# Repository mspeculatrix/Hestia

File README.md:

# HESTIA

A home robot project with the emphasis on sensors. The idea is that Hestia will autonomously patrol the home, keeping an eye on things. But it's really a way of playing with sensors.

This is a work in (slow) progress.

Hestia uses a distributed computing architecture. This consists of:

- **The Mainframe**: sounds impressive but it's probably going to be a Raspberry Pi or something similar. This does high-level stuff. It talks to...
- **Nodes**: These are microcontroller-based boards that perform specific functions, such as motor control, sensing etc. They talk to the Mainframe but also may also connect to several modules, most likely via SensorBus.
- **Modules**: These are semi-autonomous boards, each performing a single task, such as sensing, and communicating important information to (and receiving commands from) Nodes.

## CURRENT NODES

No specific Nodes have been designed so far. I've using an ATmega4809-based dev board for experimenting.

## CURRENT MODULES

- **sr04-1**: Ultrasonic rangefinder using the SensorBus HC-SR04 module board. Based on the ATtiny1604.
- **head_servo**: Uses the SensorBus servo module board to control two servos for pan & tilt operations on Hestia's sensor head. Based on the ATtiny1604.

## GIT BRANCHES

**Main**: Everything in this branch should be functional, but not necessarily complete. Basically, I use this branch as a 'safe' fallback if things go tits-up in the `dev` branch.

**dev**: This is where most of the work takes place. It always has the most up-to-date version of the project, but nothing is guaranteed to work. If you want to follow the project, this is where you should hang out.

**experimental**: For just trying stuff out, particularly stuff that I think is likely to fail. Anything in this branch should be considered temporary at best.

## OTHER REPOS FOR THIS PROJECT

- [Hestia Webserver](https://github.com/mspeculatrix/Hestia_Webserver) - a command and control server designed to be run off-robot.
- [Hestia Pico WS Server](https://github.com/mspeculatrix/Hestia_Pico_WS_Server) - a WebSocket server on the Raspberry Pi Pico 2W. Will provide an on-robot communications hub.

## SUPPORT THIS PROJECT

If you find this project in any way interesting or useful, you could consider [buying me a coffee](https://ko-fi.com/zolachrome).

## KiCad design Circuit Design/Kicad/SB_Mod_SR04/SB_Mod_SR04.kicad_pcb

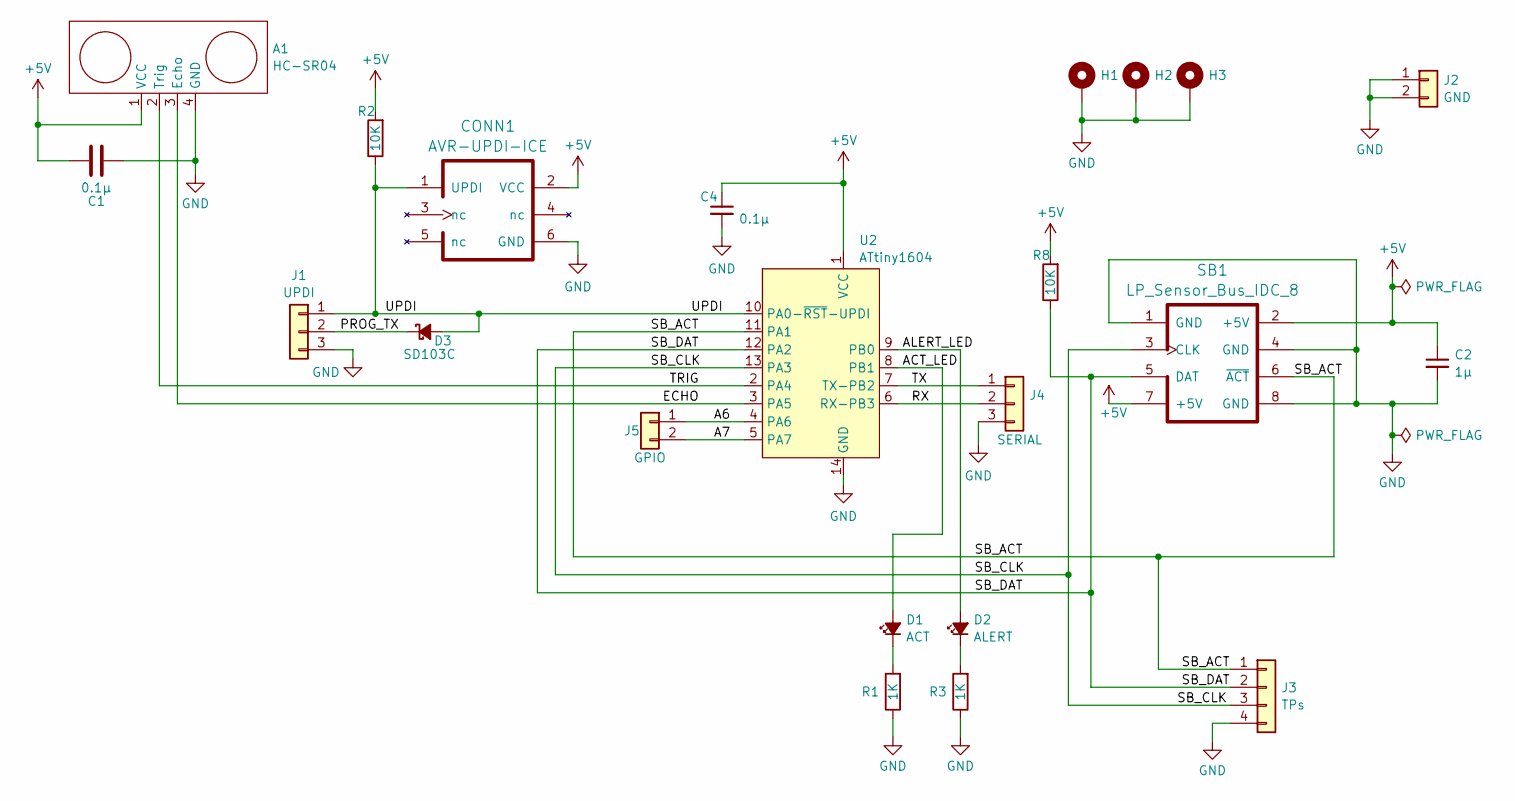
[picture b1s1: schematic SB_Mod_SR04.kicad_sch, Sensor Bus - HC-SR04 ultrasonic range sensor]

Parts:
A1: HC-SR04
C1, C4: 0.1µ; C_1206_3216Metric_Pad1.33x1.80mm_HandSolder
C2: 1µ; C_1206_3216Metric_Pad1.33x1.80mm_HandSolder
CONN1: AVR-UPDI-ICE; PinHeader_2x03_P2.54mm_Vertical
D1: ACT; LED_1206_SMD
D2: ALERT; LED_1206_SMD
D3: SD103C; D_SOD-123
H1, H2, H3: MountingHole_Pad; MountingHole_M3_Pad
J1: UPDI; PinHeader_1x03_P2.54mm_Vertical
J2: GND; PinHeader_1x02_P2.54mm_Vertical
J3: TPs; PinHeader_1x04_P2.54mm_Vertical
J4: SERIAL; PinHeader_1x03_P2.54mm_Vertical
J5: GPIO; PinHeader_1x02_P2.54mm_Vertical
R1, R3: 1K; Resistor_SMD_1206_HandSolder
R2, R8: 10K; Resistor_SMD_1206_HandSolder
SB1: LP_Sensor_Bus_IDC_8; SensorBus_2x04_P2.54mm_Vertical
U2: ATtiny1604; SOIC-14_3.9x8.7mm_P1.27mm

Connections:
+5V: A1.1 (VCC), C1.1, C2.1, C4.1, CONN1.2 (VCC), R2.2, R8.2, SB1.2 (+5V), SB1.7 (+5V), U2.1 (VCC)
/A6: J5.1, U2.4 (PA6)
/A7: J5.2, U2.5 (PA7)
/ACT_LED: D1.2 (A), U2.8 (PB1)
/ALERT_LED: D2.2 (A), U2.9 (PB0)
/ECHO: A1.3 (Echo), U2.3 (PA5)
/PROG_TX: D3.1 (K), J1.2
/RX: J4.2, U2.6 (RX-PB3)
/SB_ACT: J3.1, SB1.6 (~ACT), U2.11 (PA1)
/SB_CLK: J3.3, SB1.3 (CLK), U2.13 (PA3)
/SB_DAT: J3.2, R8.1, SB1.5 (DAT), U2.12 (PA2)
/TRIG: A1.2 (Trig), U2.2 (PA4)
/TX: J4.1, U2.7 (TX-PB2)
/UPDI: CONN1.1 (UPDI), D3.2 (A), J1.1, R2.1, U2.10 (PA0-~RST-UPDI)
GND: A1.4 (GND), C1.2, C2.2, C4.2, CONN1.6 (GND), H1.1, H2.1, H3.1, J1.3, J2.1, J2.2, J3.4, J4.3, R1.1, R3.1, SB1.1 (GND), SB1.4 (GND), SB1.8 (GND), U2.14 (GND)
unnamed: D1.1 (K), R1.2
unnamed: D2.1 (K), R3.2

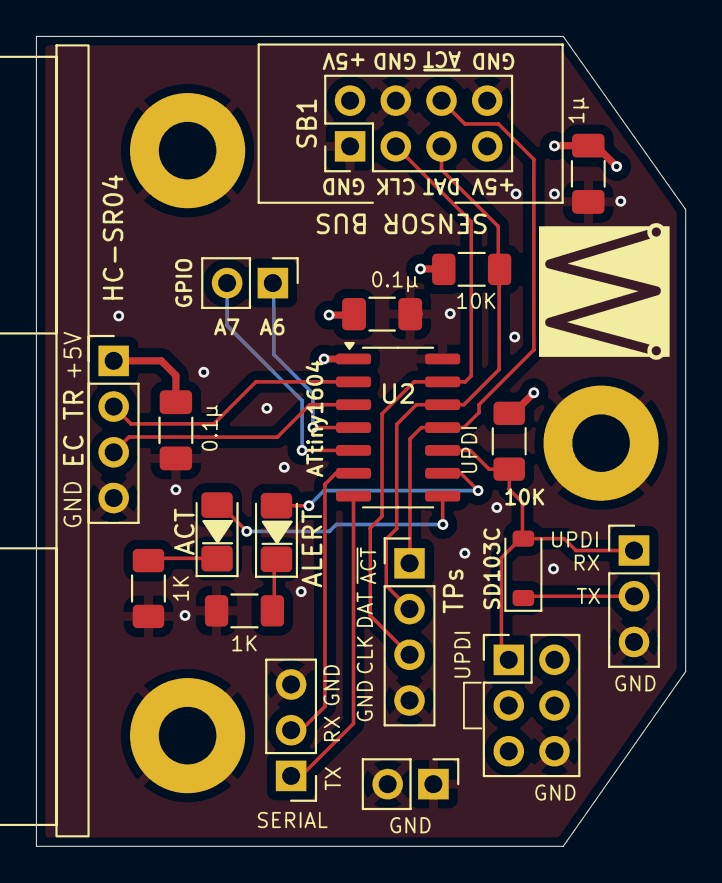
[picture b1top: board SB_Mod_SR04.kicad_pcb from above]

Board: 4 copper layers, 36.1 x 45.0 mm, 22 parts (0 on the bottom side), 17 nets.

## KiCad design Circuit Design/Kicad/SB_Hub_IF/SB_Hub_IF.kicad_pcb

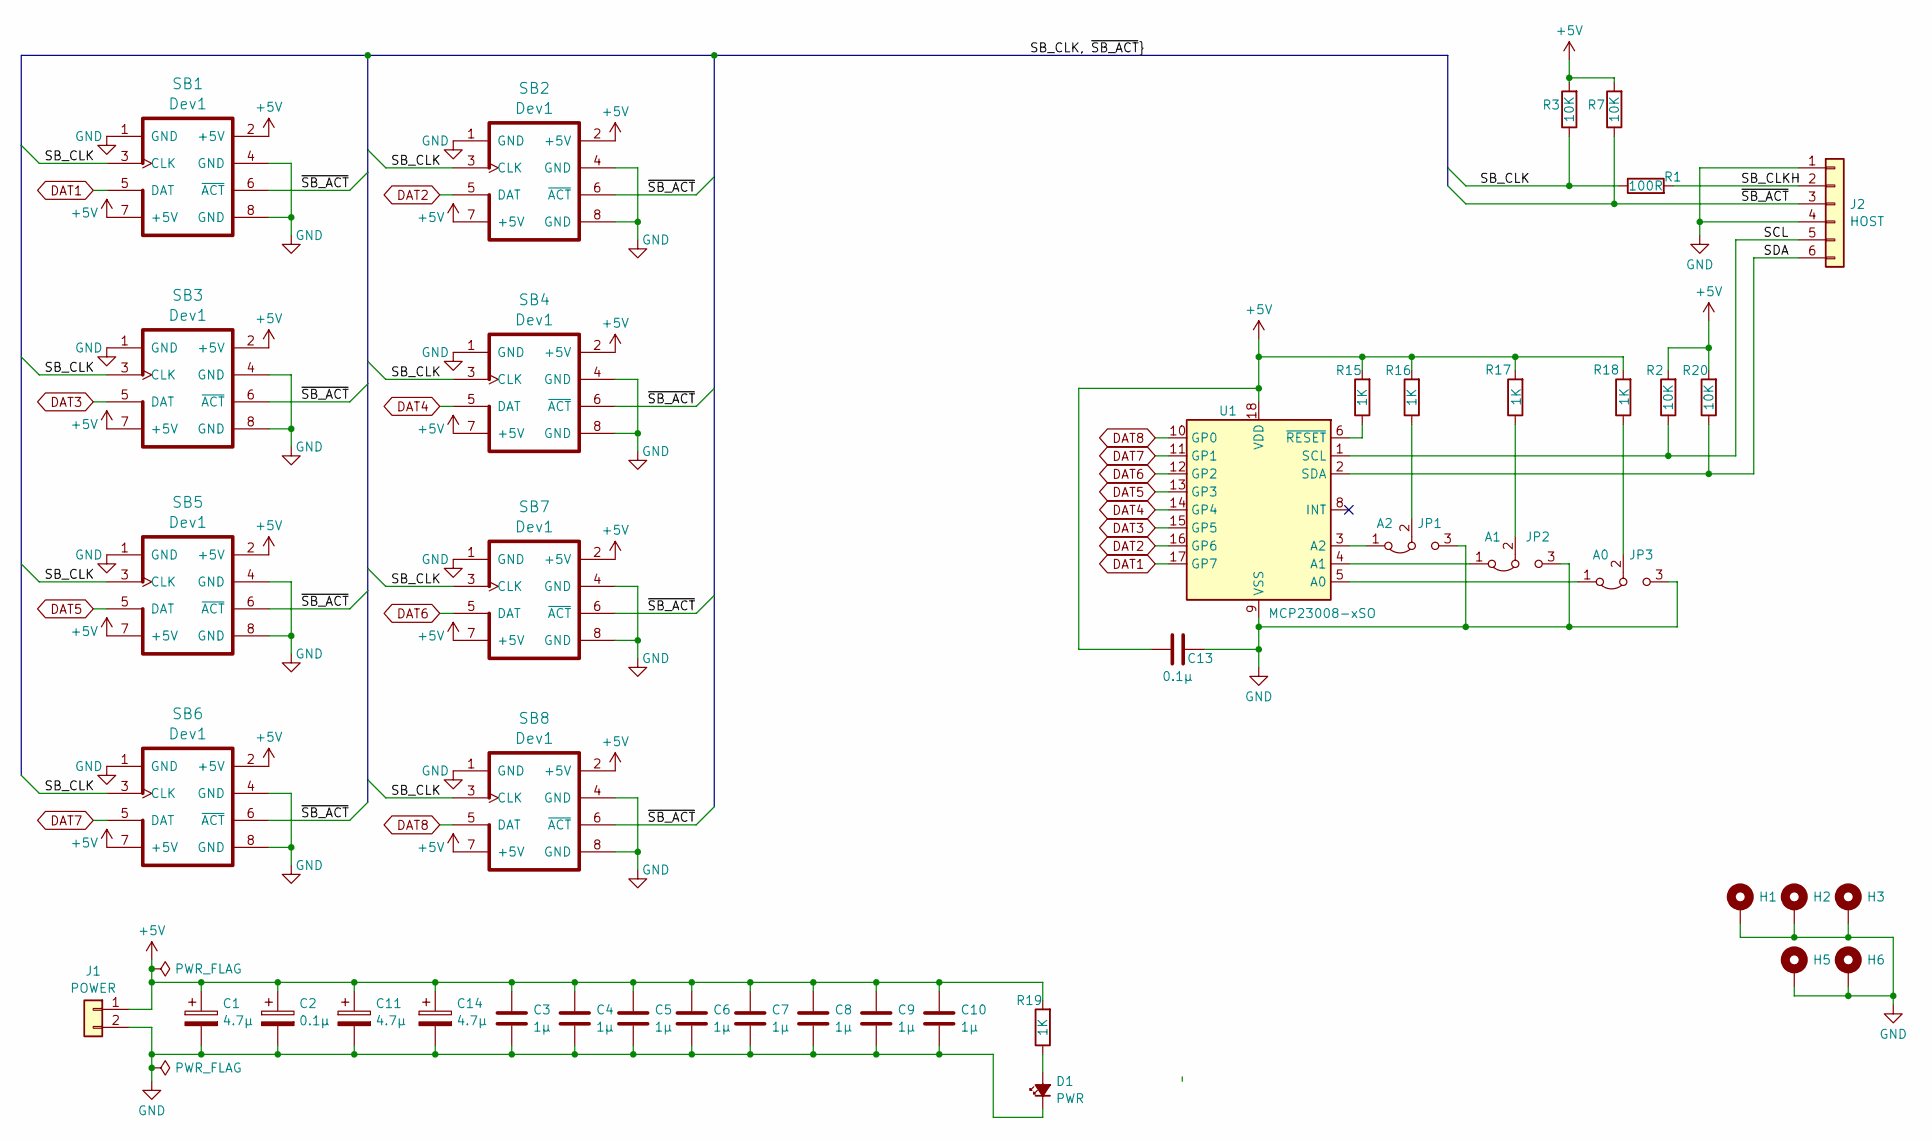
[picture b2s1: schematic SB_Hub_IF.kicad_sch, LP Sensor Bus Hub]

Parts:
C1, C11, C14: 4.7µ; Cap_THT_1µF_polarised
C2: 0.1µ; Cap_THT_0.1µF_polarised
C3, C4, C5, C6, C7, C8, C9, C10: 1µ; C_1206_3216Metric_Pad1.33x1.80mm_HandSolder
C13: 0.1µ; C_1206_3216Metric_Pad1.33x1.80mm_HandSolder
D1: PWR; LED_1206_SMD
H1, H2, H3, H5, H6: MountingHole_Pad; MountingHole_M3_Pad
J1: POWER; PinHeader_1x02_P2.54mm_Vertical
J2: HOST; PinHeader_1x06_P2.54mm_Horizontal
JP1: A2; PinHeader_1x03_P2.54mm_Vertical
JP2: A1; PinHeader_1x03_P2.54mm_Vertical
JP3: A0; PinHeader_1x03_P2.54mm_Vertical
R1: 100R; Resistor_SMD_1206_HandSolder
R2, R3, R7, R20: 10K; Resistor_SMD_1206_HandSolder
R15, R16, R17, R18, R19: 1K; Resistor_SMD_1206_HandSolder
SB1, SB2, SB3, SB4, SB5, SB6, SB7, SB8: Dev1; SensorBus_2x04_P2.54mm_Vertical
U1: MCP23008-xSO; SOIC-18W_7.5x11.6mm_P1.27mm

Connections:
+5V: C1.1, C2.1, C3.1, C4.1, C5.1, C6.1, C7.1, C8.1, C9.1, C10.1, C11.1, C13.1, C14.1, J1.1, R2.2, R3.2, R7.2, R15.2, R16.2, R17.2, R18.2, R19.2, R20.2, SB1.2 (+5V), SB1.7 (+5V), SB2.2 (+5V), SB2.7 (+5V), SB3.2 (+5V), SB3.7 (+5V), SB4.2 (+5V), SB4.7 (+5V), SB5.2 (+5V), SB5.7 (+5V), SB6.2 (+5V), SB6.7 (+5V), SB7.2 (+5V), SB7.7 (+5V), SB8.2 (+5V), SB8.7 (+5V), U1.18 (VDD)
/SB_CLK: R1.1, R3.1, SB1.3 (CLK), SB2.3 (CLK), SB3.3 (CLK), SB4.3 (CLK), SB5.3 (CLK), SB6.3 (CLK), SB7.3 (CLK), SB8.3 (CLK)
/SB_CLKH: J2.2, R1.2
/SCL: J2.5, R2.1, U1.1 (SCL)
/SDA: J2.6, R20.1, U1.2 (SDA)
/~SB_ACT: J2.3, R7.1, SB1.6 (~ACT), SB2.6 (~ACT), SB3.6 (~ACT), SB4.6 (~ACT), SB5.6 (~ACT), SB6.6 (~ACT), SB7.6 (~ACT), SB8.6 (~ACT)
DAT1: SB1.5 (DAT), U1.17 (GP7)
DAT2: SB2.5 (DAT), U1.16 (GP6)
DAT3: SB3.5 (DAT), U1.15 (GP5)
DAT4: SB4.5 (DAT), U1.14 (GP4)
DAT5: SB5.5 (DAT), U1.13 (GP3)
DAT6: SB7.5 (DAT), U1.12 (GP2)
DAT7: SB6.5 (DAT), U1.11 (GP1)
DAT8: SB8.5 (DAT), U1.10 (GP0)
GND: C1.2, C2.2, C3.2, C4.2, C5.2, C6.2, C7.2, C8.2, C9.2, C10.2, C11.2, C13.2, C14.2, D1.1 (K), H1.1, H2.1, H3.1, H5.1, H6.1, J1.2, J2.1, J2.4, JP1.3 (B), JP2.3 (B), JP3.3 (B), SB1.1 (GND), SB1.4 (GND), SB1.8 (GND), SB2.1 (GND), SB2.4 (GND), SB2.8 (GND), SB3.1 (GND), SB3.4 (GND), SB3.8 (GND), SB4.1 (GND), SB4.4 (GND), SB4.8 (GND), SB5.1 (GND), SB5.4 (GND), SB5.8 (GND), SB6.1 (GND), SB6.4 (GND), SB6.8 (GND), SB7.1 (GND), SB7.4 (GND), SB7.8 (GND), SB8.1 (GND), SB8.4 (GND), SB8.8 (GND), U1.9 (VSS)
unnamed: D1.2 (A), R19.1
unnamed: JP1.1 (A), U1.3 (A2)
unnamed: JP1.2 (C), R16.1
unnamed: JP2.1 (A), U1.4 (A1)
unnamed: JP2.2 (C), R17.1
unnamed: JP3.1 (A), U1.5 (A0)
unnamed: JP3.2 (C), R18.1
unnamed: R15.1, U1.6 (~RESET)

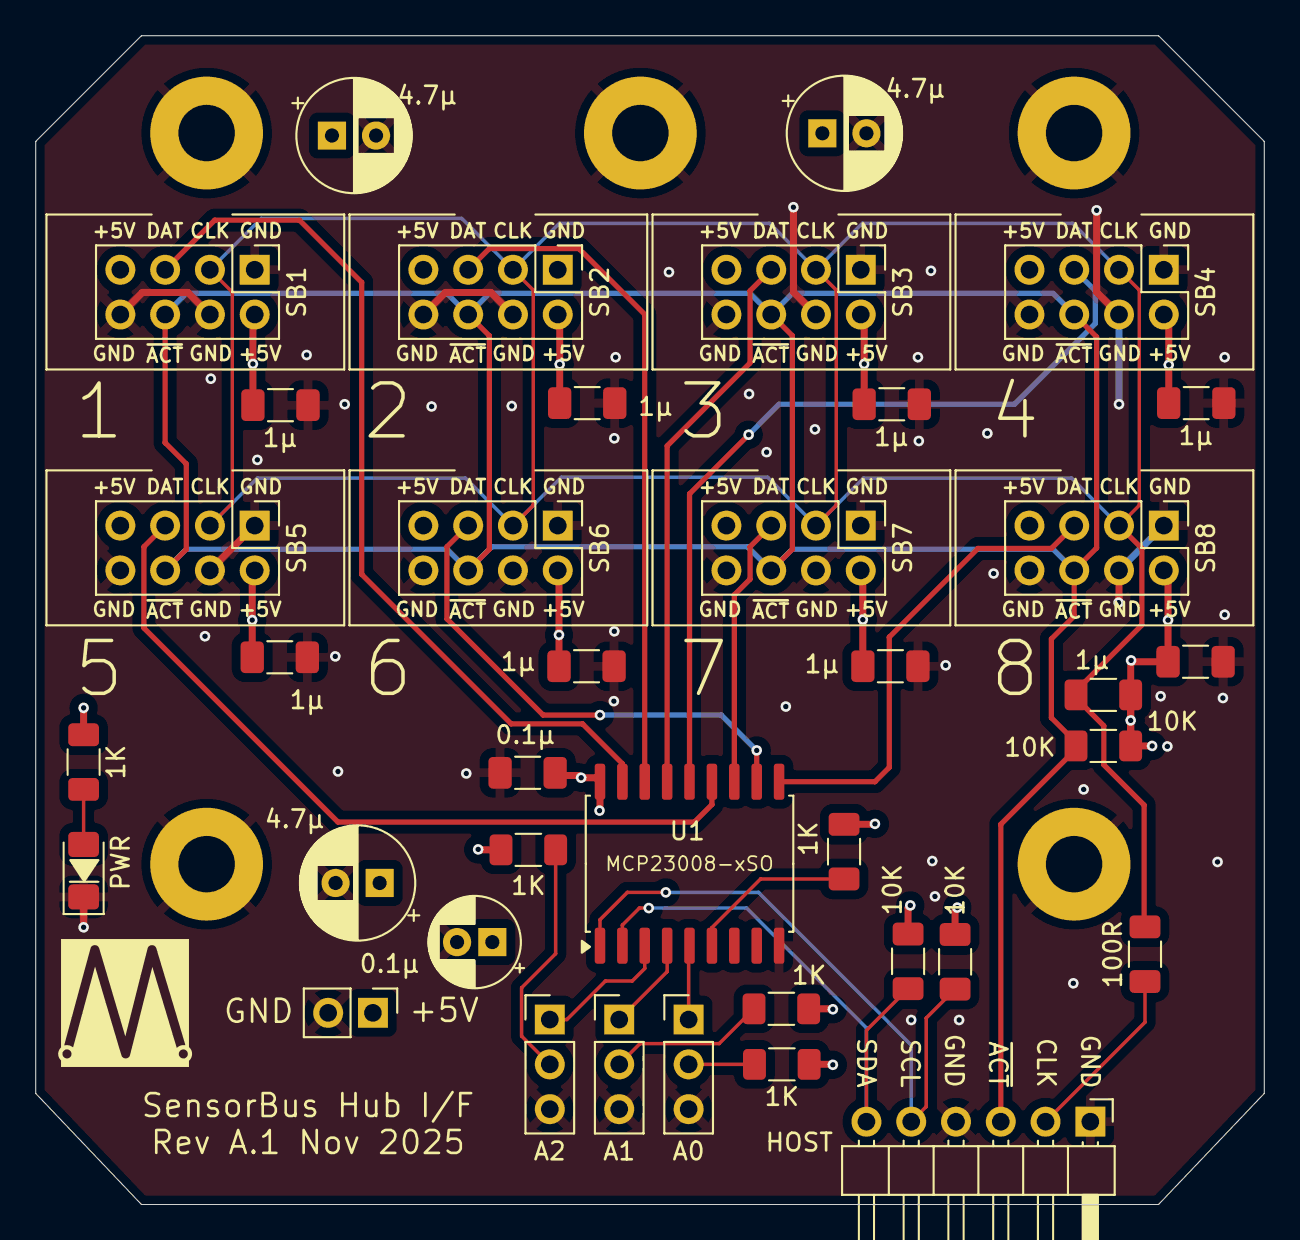
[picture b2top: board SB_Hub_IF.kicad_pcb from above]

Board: 4 copper layers, 69.7 x 66.3 mm, 43 parts (0 on the bottom side), 23 nets.

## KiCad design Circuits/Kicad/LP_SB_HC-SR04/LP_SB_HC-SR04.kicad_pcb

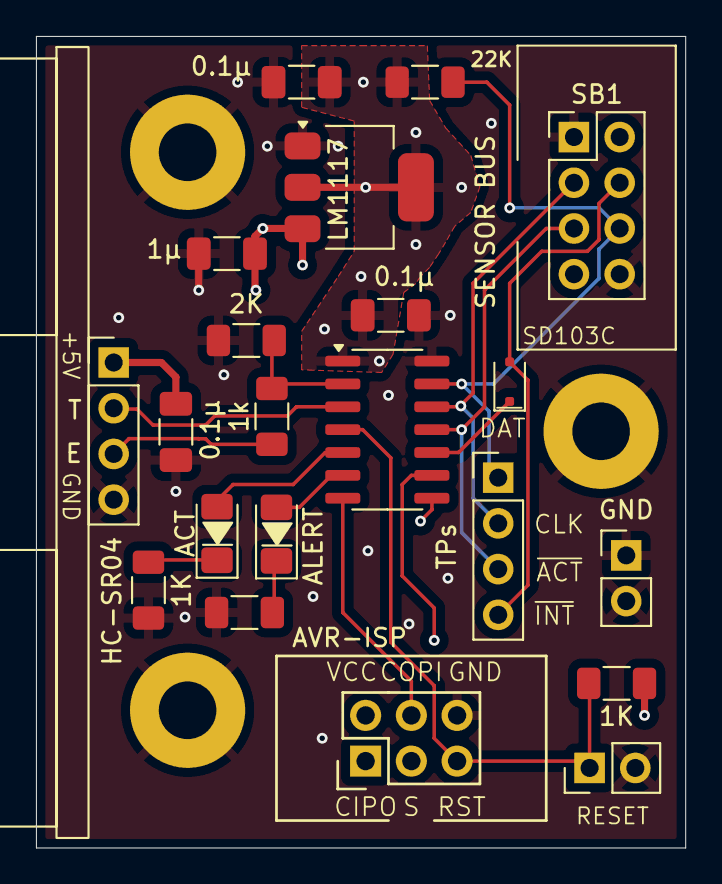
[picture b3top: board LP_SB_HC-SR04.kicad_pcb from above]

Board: 4 copper layers, 36.1 x 45.1 mm, 24 parts (0 on the bottom side), 19 nets.

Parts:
A1: HC-SR04
C1, C4, C5: 0.1µ; C_1206_3216Metric_Pad1.33x1.80mm_HandSolder
C2: 1µ; C_1206_3216Metric_Pad1.33x1.80mm_HandSolder
CONN1: AVR-ISP; AVR_ISP_HE10_2x3
D1: ACT; LED_1206_SMD
D2: ALERT; LED_1206_SMD
D3: SD103C; D_SOD-323F
H1, H2, H3: MountingHole_Pad; MountingHole_M3_Pad
J1: TPs; PinHeader_1x04_P2.54mm_Vertical
J2: GND; PinHeader_1x02_P2.54mm_Vertical
J3: RESET; PinHeader_1x02_P2.54mm_Vertical
LM1: LM1117; SOT-223-3_TabPin2
R1, R2, R3: 1K; Resistor_SMD_1206_HandSolder
R8: 22K; Resistor_SMD_1206_HandSolder
R9: 1k; Resistor_SMD_1206_HandSolder
R10: 2K; Resistor_SMD_1206_HandSolder
SB1: LP_Sensor_Bus_IDC_8; SensorBus_2x04_P2.54mm_Vertical
U1: ATTINY84A; SOIC-14_3.9x8.7mm_P1.27mm

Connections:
+3V3: C4.1, C5.2, LM1.2 (Vout), R2.2, R8.2, U1.1 (VCC)
+5V: A1.1 (VCC), C1.1, C2.1, CONN1.2 (VCC), LM1.3 (Vin), SB1.2 (+5V), SB1.7 (+5V)
/ACT_LED: D1.2 (A), U1.5 (PB2)
/ALERT_LED: D2.2 (A), U1.6 (PA7)
/CIPO: CONN1.1 (CIPO), U1.8 (PA5)
/COPI: CONN1.4 (COPI), U1.7 (PA6)
/ECHO_H: A1.3 (Echo), R9.2
/ECHO_L: R9.1, R10.2, U1.2 (PB0)
/SB_CLK: J1.2, SB1.3 (CLK), U1.12 (PA1)
/SB_DAT: J1.1, R8.1, SB1.6 (DAT), U1.13 (PA0)
/SCK: CONN1.3 (SCK), U1.9 (PA4)
/TRIG: A1.2 (Trig), U1.3 (PB1)
/~RESET: CONN1.5 (RESET), J3.1, R2.1, U1.4 (PB3)
/~SB_ACT: J1.3, SB1.5 (~ACT), U1.11 (PA2)
/~SB_INT: D3.2 (A), J1.4, SB1.4 (~INT)
/~SB_INTP: D3.1 (K), U1.10 (PA3)
GND: A1.4 (GND), C1.2, C2.2, C4.2, C5.1, CONN1.6 (GND), H1.1, H2.1, H3.1, J2.1, J2.2, J3.2, LM1.1 (GND), R1.1, R3.1, R10.1, SB1.1 (GND), SB1.8 (GND), U1.14 (GND)
unnamed: D1.1 (K), R1.2
unnamed: D2.1 (K), R3.2

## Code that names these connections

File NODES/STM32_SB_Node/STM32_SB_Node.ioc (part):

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Mcu.Name=STM32H503RBTx
Mcu.Package=LQFP64
Mcu.UserName=STM32H503RBTx
PA13(JTMS/SWDIO).GPIOParameters=GPIO_Label
PA13(JTMS/SWDIO).GPIO_Label=T_SWDIO
PA13(JTMS/SWDIO).Signal=DEBUG_JTMS-SWDIO
PA14(JTCK/SWCLK).GPIOParameters=GPIO_Label
PA14(JTCK/SWCLK).GPIO_Label=T_SWCLK
PA14(JTCK/SWCLK).Signal=DEBUG_JTCK-SWCLK
PA15(JTDI).GPIOParameters=GPIO_Label
PA15(JTDI).GPIO_Label=T_JTDI
PA15(JTDI).Signal=DEBUG_JTDI
PA3.Signal=USART3_RX
PA4.Signal=USART3_TX
PB14.GPIOParameters=GPIO_Label
PB14.GPIO_Label=ARD_D1_TX
PB14.Signal=USART1_TX
PB15.GPIOParameters=GPIO_Label
PB15.GPIO_Label=ARD_D0_RX
PB15.Signal=USART1_RX
PB3(JTDO/TRACESWO).GPIOParameters=GPIO_Label
PB3(JTDO/TRACESWO).GPIO_Label=T_SWO
PB3(JTDO/TRACESWO).Signal=DEBUG_JTDO-SWO
PC0.GPIOParameters=GPIO_Label
PC0.GPIO_Label=SB_CLK
PC0.Signal=GPIO_Input
PC1.GPIOParameters=GPIO_Label
PC1.GPIO_Label=SB_ACT
PC1.Signal=GPIO_Input
PC10.GPIOParameters=GPIO_PuPd,GPIO_Label,GPIO_ModeDefaultEXTI
PC10.GPIO_Label=DAT2
PC10.GPIO_ModeDefaultEXTI=GPIO_MODE_IT_FALLING
PC10.GPIO_PuPd=GPIO_PULLUP
PC10.Signal=GPXTI10
PC11.GPIOParameters=GPIO_PuPd,GPIO_Label,GPIO_ModeDefaultEXTI
PC11.GPIO_Label=DAT3
PC11.GPIO_ModeDefaultEXTI=GPIO_MODE_IT_FALLING
PC11.GPIO_PuPd=GPIO_PULLUP
PC11.Signal=GPXTI11
PC12.GPIOParameters=GPIO_PuPd,GPIO_Label,GPIO_ModeDefaultEXTI
PC12.GPIO_Label=DAT4
PC12.GPIO_ModeDefaultEXTI=GPIO_MODE_IT_FALLING
PC12.GPIO_PuPd=GPIO_PULLUP
PC12.Signal=GPXTI12
PC13.GPIOParameters=GPIO_PuPd,GPIO_Label,GPIO_ModeDefaultEXTI
PC13.GPIO_Label=DAT5
PC13.GPIO_ModeDefaultEXTI=GPIO_MODE_IT_FALLING
PC13.GPIO_PuPd=GPIO_PULLUP
PC13.Signal=GPXTI13
PC14-OSC32_IN(OSC32_IN).GPIOParameters=GPIO_PuPd,GPIO_Label,GPIO_ModeDefaultEXTI
PC14-OSC32_IN(OSC32_IN).GPIO_Label=DAT6
PC14-OSC32_IN(OSC32_IN).GPIO_ModeDefaultEXTI=GPIO_MODE_IT_FALLING
PC14-OSC32_IN(OSC32_IN).GPIO_PuPd=GPIO_PULLUP
PC14-OSC32_IN(OSC32_IN).Signal=GPXTI14
PC15-OSC32_OUT(OSC32_OUT).GPIOParameters=GPIO_PuPd,GPIO_Label,GPIO_ModeDefaultEXTI
PC15-OSC32_OUT(OSC32_OUT).GPIO_Label=DAT7
PC15-OSC32_OUT(OSC32_OUT).GPIO_ModeDefaultEXTI=GPIO_MODE_IT_FALLING
PC15-OSC32_OUT(OSC32_OUT).GPIO_PuPd=GPIO_PULLUP
PC15-OSC32_OUT(OSC32_OUT).Signal=GPXTI15
PC8.GPIOParameters=GPIO_PuPd,GPIO_Label,GPIO_ModeDefaultEXTI
PC8.GPIO_Label=DAT0
PC8.GPIO_ModeDefaultEXTI=GPIO_MODE_IT_FALLING
PC8.GPIO_PuPd=GPIO_PULLUP
PC8.Signal=GPXTI8
PC9.GPIOParameters=GPIO_PuPd,GPIO_Label,GPIO_ModeDefaultEXTI
PC9.GPIO_Label=DAT1
PC9.GPIO_ModeDefaultEXTI=GPIO_MODE_IT_FALLING
PC9.GPIO_PuPd=GPIO_PULLUP
PC9.Signal=GPXTI9
PH0-OSC_IN(PH0).Mode=HSE-External-Oscillator
PH0-OSC_IN(PH0).Signal=RCC_OSC_IN
PH1-OSC_OUT(PH1).Mode=HSE-External-Oscillator
PH1-OSC_OUT(PH1).Signal=RCC_OSC_OUT
RCC.HSE_VALUE=24000000
RCC.SYSCLKFreq_VALUE=250000000
RCC.SYSCLKSource=RCC_SYSCLKSOURCE_PLLCLK
board=NUCLEO-H503RB
boardIOC=true

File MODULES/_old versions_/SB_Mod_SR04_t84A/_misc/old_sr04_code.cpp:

/*
 * SmartHCSR04.cpp
 *
 * Created: 11/27/2018 12:32:39 PM
 * Author : Steve
 */
#ifndef F_CPU
#define F_CPU 1000000UL
#endif

#include <avr/io.h>
#include <util/delay.h>
#include <string.h>
#include <stdio.h>
#include <smd_avr_usi_i2clib.h>
#include <uproc/smd_attiny_24_44_84A.h>
 //#include <smd_avr_sensorbuslib.h>

#define TRIG_PIN PA1			// orange
#define ECHO_PIN PA2			// yellow
#define ALERT_PIN PA3			// goes low to alert hub
#define LCD_I2C_ADDR 0xC6
#define MAX_ECHO_TIME 23200		// 23200us is 400cm max range.
#define DIST_FACTOR 58

#define ALERT_PULSE_TIME 50		// us
#define ALERT_INTERVAL 500		// ms - minimum time between alert signals - blocking

#define DEFAULT_ALERT_DIST 15	// cm

void displayMsg(const char msg[], uint8_t x, uint8_t y) {
	USI_I2C_start(LCD_I2C_ADDR, I2C_WRITE_MODE);
	USI_I2C_sendByte(0);	// command register
	USI_I2C_sendByte(3);	// position cursor command
	USI_I2C_sendByte(y);	// x pos : first col
	USI_I2C_sendByte(x);	// y pos
	for (uint8_t i = 0; i < strlen(msg); i++) {
		USI_I2C_sendByte(char(msg[i]));
	}
	// clear rest of line with spaces
	//for(uint8_t i = strlen(msg); i < 12; i++) {
	//USI_I2C_sendByte(0x20);	// space
	//}
	USI_I2C_stop();
}

void displayClear() {
	USI_I2C_start(LCD_I2C_ADDR, I2C_WRITE_MODE);
	USI_I2C_sendByte(0);	// command register
	USI_I2C_sendByte(12);
	USI_I2C_stop();
}

void displayInit() {
	USI_I2C_start(LCD_I2C_ADDR, I2C_WRITE_MODE);
	USI_I2C_sendByte(0);	// command register
	USI_I2C_sendByte(4);	// cursor off
	USI_I2C_sendByte(12);	// clear screen, home cursor
	USI_I2C_sendByte(19);	// backlight on
	USI_I2C_stop();
}

uint16_t ping(void) {
	unsigned long elapsed = 0;
	uint16_t distance = 0;
	PORTA |= (1 << TRIG_PIN);				// set trigger pin high
	_delay_us(10);							// wait for min. 10us
	PORTA &= ~(1 << TRIG_PIN);				// take trigger pin low again
	while ((PINA & (1 << ECHO_PIN)) == 0);	// loop until echo pin goes high
	TCNT1 = 0;								// reset timer
	while (PINA & (1 << ECHO_PIN));			// loop until echo pin goes low again
	elapsed = TCNT1;						// read timer
	// at clock speed of 1MHz, elapsed will be number of us for echo time.
	// This should be well within range of 16-bit int (TCNT1 is 16-bit).
	// With higher clock speeds, elapsed is going to be much higher and
	// may need scaling
	elapsed = elapsed / (F_CPU / 1000000.0);	// to scale for clock speed, but here we're diving by 1 !
	if (elapsed <= MAX_ECHO_TIME) {
		distance = (uint16_t)(elapsed / DIST_FACTOR);
	}
	return distance;
}

// MAIN OBJECTS
//SensorBus ssb = SensorBus();

int main(void) {
	// ----------------------------------------------------------------------------------------------------
	// -----  SETUP                                                                                   -----
	// ----------------------------------------------------------------------------------------------------
	DDRA = 0;	// actually defaults to this, but let's be specific
	DDRA |= (1 << TRIG_PIN);		// Trigger pin as output
	DDRA |= (1 << ALERT_PIN);		// Alert pin as output
	PORTA &= ~(1 << TRIG_PIN);		// set trigger pin low
	PORTA |= (1 << ALERT_PIN);		// set alert pin high (it's active low)
	TCCR1B |= (1 << CS10);			// set prescaler to clk/1 (no prescaling)


	//ssb.init();
	//ssb.addChannel(PCINT3);
	USI_I2C_initialiseBus();
	displayInit();
	char display_buf[21];
	//displayMsg("Echo:",1,1);
	//displayMsg("us",13,1);
	displayMsg("Dist:", 1, 2);
	displayMsg("cm", 13, 2);
	uint16_t dist = 0;
	//bool alerted = FALSE;
	while (1) {
		dist = ping();
		if (dist < DEFAULT_ALERT_DIST) {
			PORTA &= ~(1 << ALERT_PIN);		// take alert pin low
			//_delay_us(ALERT_PULSE_TIME);	// make sure we get noticed
			//alerted = TRUE;
			_delay_ms(ALERT_INTERVAL);		// delay to avoid sending too many alerts
			PORTA |= (1 << ALERT_PIN);		// take it high again
		}
		//sprintf(display_buf, "%5u", echoTime);
		//displayMsg(display_buf,7,1);
		sprintf(display_buf, "%3i", dist);
		displayMsg(display_buf, 9, 2);
		_delay_ms(100);
	}
}

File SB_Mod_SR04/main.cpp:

/*
 * LP_SB_SR04
 *
 * Ultrasonic rangefinder using the Sensor Bus
 *
 */

#define DEBUG true

#ifndef __AVR_ATtiny84A__
#define __AVR_ATtiny84A__
#endif

#ifndef F_CPU
#define F_CPU 1000000UL // define it now as 16 MHz unsigned long
#endif

#ifndef __OPTIMIZE__
#define __OPTIMIZE__
#endif

#define __DELAY_BACKWARD_COMPATIBLE__ // fix problem with _delay_ms()

#include <avr/io.h>
#include <stdio.h>
#include <avr/interrupt.h>
#include <util/delay.h>

#include "lib/defines.h"
#include "lib/functions.h"
#include "lib/smd_std_macros.h"
#include "lib/smd_std_typedefs.h"
#include "lib/smd_attiny_24_44_84A.h"

 /* GLOBALS */
volatile bool exchangeInit = false;
uint8_t outMsgBuf[MSG_BUF_LEN];
uint8_t inMsgBuf[MSG_BUF_LEN];

// -----  FUNCTIONS  -----------------------------------------------------------

void receiveMessage() {
	uint8_t msgLen = MSG_BUF_LEN;
	uint8_t bitIdx = 0;
	uint8_t byteIdx = 0;
	bool msgEnd = false;
	while (!msgEnd) {
		while (bit_is_set(PORTA, SB_CLK)) {} 	// Wait for SB_CLK LOW
		if (bit_is_set(PORTA, SB_DAT)) {		// Read bit
			inMsgBuf[byteIdx] |= (1 << bitIdx);
		} else {
			inMsgBuf[byteIdx] &= ~(1 << bitIdx);
		}
		bitIdx++;
		if (bitIdx == 8) {						// We've got a byte's worth
			if (byteIdx = 0) { 					// This is the first byte
				msgLen = inMsgBuf[byteIdx];
			}
			byteIdx++;
			if (byteIdx == msgLen) {
				msgEnd = true;
			} else {
				bitIdx = 0;
			}
		}
		while (bit_is_clear(PORTA, SB_CLK)) {} 	// Wait for SB_CLK HIGH
	}



	for (uint8_t idx = 0; idx < MSG_BUF_LEN; idx++) {
		for (uint8_t bit = 0; bit < 8; bit++) {

			while (bit_is_clear(PORTA, SB_CLK)) {}// Wait for SB_CLK HIGH
		}
	}
}

void sendMessage() {
	uint8_t msgIdx = 0;
	for (uint8_t idx = 0; idx < MSG_BUF_LEN; idx++) {
		for (uint8_t bit = 0; bit < 8; bit++) {
			uint8_t bitval = (outMsgBuf[idx] & (1 << bit)) >> bit;
			if (bitval == 1) {
				SETBIT(PORTA, SB_DAT);
			} else {
				CLEARBIT(PORTA, SB_DAT);
			}
			_delay_ms(BIT_PAUSE);
			CLEARBIT(PORTA, SB_CLK);
			_delay_ms(BIT_PAUSE);
			SETBIT(PORTA, SB_CLK);
		}
		_delay_ms(BYTE_PAUSE);
	}
}

void setReceiveMode() {
	DAT_INT_DISABLE;						// Disable SB_DAT interrupts
	SET_DAT_OUTPUT;
	CLEARBIT(PORTA, SB_DAT);
	_delay_ms(DAT_PULSE_LENGTH);
	SETBIT(PORTA, SB_DAT);
	SET_DAT_INPUT;
	// DDRA &= ~(1 << SB_CLK);				// Set /SB_CLK to INPUT
}

uint8_t setSendMode() {
	uint8_t error = 0;
	uint8_t initAttempts = 0;
	while (error == 0) {
		initAttempts++;
		if (bit_is_set(PINA, SB_CLK)) { 			// clock is high so let's try
			DAT_INT_DISABLE;						// Disable DAT interrupts
			SET_DAT_OUTPUT;
			SETBIT(PORTA, SB_DAT);
			CLEARBIT(PORTA, SB_DAT);				// Strobe DAT line
			_delay_ms(DAT_PULSE_LENGTH);
			SETBIT(PORTA, SB_DAT);
			SET_DAT_INPUT;

			// Wait for `SB_DAT` to pulse LOW

			bool loop = true;
			uint8_t attempts = 0;
			while (loop) {
				if (bit_is_set(PINA, SB_DAT)) {
					_delay_ms(TIMEOUT_LOOP_DELAY);
					attempts++;
					if (attempts == MAX_CONNECTION_ATTEMPTS) {
						loop = false;
						error = ERR_MAX_ATTEMPTS;
					}
				} else {			// DAT has gone low
					loop = false;
					// setPin(&PORTA, SB_DAT, HIGH);
					SET_DAT_OUTPUT;
					SET_CLK_OUTPUT;
					SETBIT(PORTA, SB_DAT);
					SETBIT(PORTA, SB_CLK);
					_delay_ms(STABILISE_DELAY); 			// let hub get ready
				}
			}
		} else if (initAttempts < MAX_INIT_ATTEMPTS) {
			_delay_ms(INIT_RETRY_DELAY);
		} else {
			error = ERR_HUB_NOT_RESPONDING;
		}
	}
	return error;
}

void setSBDefaultState() {
	DDRA &= ~(1 << SB_CLK | 1 << SB_DAT);	// Set SB pins as inputs
	DAT_INT_ENABLE;							// Enable interrupts on SB_DAT
}

// -----  Interrupt Service Routine  -------------------------------------------
ISR(PCINT0_vect) {
	// This responds to any PC interrupts 0-7. But as we're using only PCINT0
	// then we can be sure that's the pin on which the interrupt occurred.
	DAT_INT_DISABLE;						// Disable interrupts on SB_DAT
	exchangeInit = true;					// Controller has pulsed SB_DAT low
	if (DEBUG) {
		setPin(&PORTB, ACT_LED, HIGH);			// Flash LED
		_delay_ms(50);
		setPin(&PORTB, ACT_LED, LOW);
	}
}

// =============================================================================
// =====   MAIN                                                            =====
// =============================================================================
int main(void) {

	/***************************************************************************
	*****   SETUP                                                          *****
	***************************************************************************/

	setSBDefaultState();		// Sets SB lines (Port A) to defaults (inputs)
	DDRA |= (1 << ALERT_LED);	// ALERT_LED, SB_INT to outputs
	DDRB |= (1 << ACT_LED | 1 << TRIGGER); 	// LED and TRIGGER to outputs
	setPin(&PORTB, ACT_LED, LOW);
	setPin(&PORTA, ALERT_LED, LOW);
	setPin(&PORTB, TRIGGER, LOW);

	// Set up interrupts
	GIMSK |= (1 << PCIE0);						// Enable PC interrupts 0-7
	DAT_INT_ENABLE;								// Enable interrupts on SB_DAT

	flashActive(5);
	flashAlert(5);

	sei();									// Turn interrupts on

	/***************************************************************************
	*****   MAIN LOOP                                                      *****
	***************************************************************************/


	while (1) {
		// if (exchangeInit) {
		// exchangeInit = false;
		// DAT_INT_ENABLE;
		// }
		for (uint8_t byte0 = 64; byte0 < 128; byte0++) {
			outMsgBuf[0] = MSG_BUF_LEN;
			for (uint8_t byte1 = 64; byte1 < 128; byte1++) {
				outMsgBuf[1] = byte1;
				for (uint8_t byte2 = 64; byte2 < 128; byte2++) {
					outMsgBuf[2] = byte2;
					setSendMode();
					sendMessage();
					setSBDefaultState();
					_delay_ms(1000);
					flashAlert(1);
				}
			}
		}
	}

}

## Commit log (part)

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2025-09-13 Renamed to Hestia
2025-09-16 Update before creating dev branch
2025-10-22 Tidy up
2025-10-25 Working Sensor Bus; prior to merge with main
2025-10-27 Class-based version of SR04 code. Pausing that here for now.
2025-12-12 Reorganised
2025-12-23 SB_Mod_SR04
2025-12-23 Modified .gitignore
2025-12-23 Changed .gitignore
2025-12-23 Untrack numbers files
2025-12-23 Untrack files
2025-12-23 Pre-merge
2025-12-24 SR04 basic functionality working
2025-12-24 Recovered files
2025-12-26 Working SR04 mod with PIT timer
2025-12-26 Tidied up comments etc
2026-01-08 So many things
2026-01-21 SensorBus working
2026-01-22 tidy up before merge into main
2026-01-24 SB working both directions
2026-01-26 Pre-merge into main
2026-01-28 Working servo; doc changes
2026-01-29 Node app now sends correct msg for servo
2026-02-07 Crreated specific head node and head servo module
2026-02-10 Reorganised modules & nodes
2026-03-09 Reworked modules
2026-04-21 Initial setup for STM32-based node
